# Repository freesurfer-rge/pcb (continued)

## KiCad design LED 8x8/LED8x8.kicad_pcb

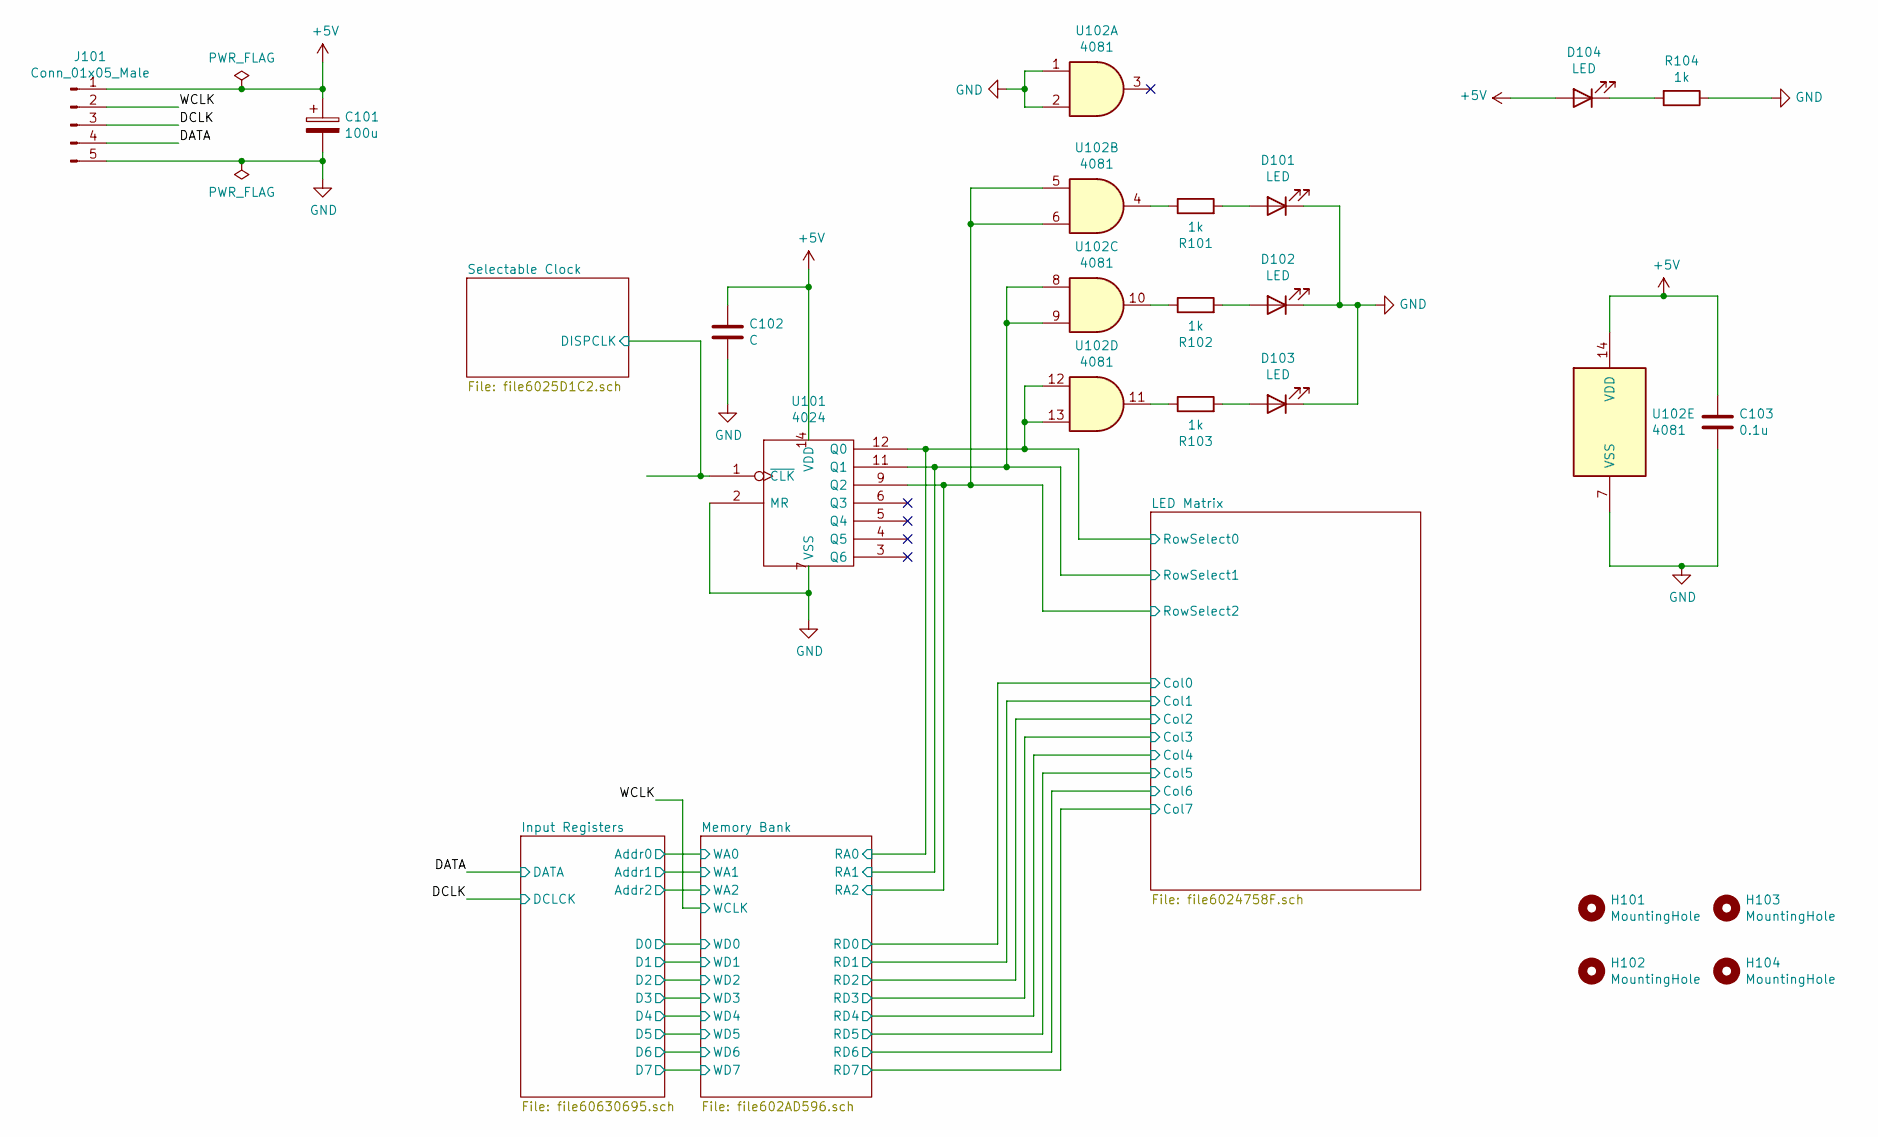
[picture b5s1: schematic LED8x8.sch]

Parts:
C101: 100u; CP_Radial_D5.0mm_P2.50mm
C102: C; C_Disc_D4.7mm_W2.5mm_P5.00mm
C103: 0.1u; C_Disc_D4.7mm_W2.5mm_P5.00mm
D101, D102, D103: LED; LED_D3.0mm
D104: LED; LED_D5.0mm
H101, H102, H103, H104: MountingHole; MountingHole_2.7mm_M2.5
J101: Conn_01x05_Male; PinHeader_1x05_P2.54mm_Vertical
R101, R102, R103, R104: 1k; R_Axial_DIN0207_L6.3mm_D2.5mm_P7.62mm_Horizontal
U101: 4024; DIP-14_W7.62mm_Socket
U102: 4081

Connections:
+5V: C101.1, C102.2, C103.2, D104.2 (A), J101.1, U101.14 (VDD), U102.14 (VDD); also elsewhere on the board
/DATA: J101.4; also elsewhere on the board
/DCLK: J101.3; also elsewhere on the board
/Memory Bank/RA0: U101.12 (Q0), U102.12, U102.13; also elsewhere on the board
/Memory Bank/RA1: U101.11 (Q1), U102.8, U102.9; also elsewhere on the board
/Memory Bank/RA2: U101.9 (Q2), U102.5, U102.6; also elsewhere on the board
/Selectable Clock/DISPCLK: U101.1 (~CLK); also elsewhere on the board
/WCLK: J101.2; also elsewhere on the board
GND: C101.2, C102.1, C103.1, D101.1 (K), D102.1 (K), D103.1 (K), J101.5, R104.1, U101.2 (MR), U101.7 (VSS), U102.1, U102.2, U102.7 (VSS); also elsewhere on the board
unnamed: D101.2 (A), R101.2
unnamed: D102.2 (A), R102.2
unnamed: D103.2 (A), R103.2
unnamed: D104.1 (K), R104.2
unnamed: R101.1, U102.4
unnamed: R102.1, U102.10
unnamed: R103.1, U102.11

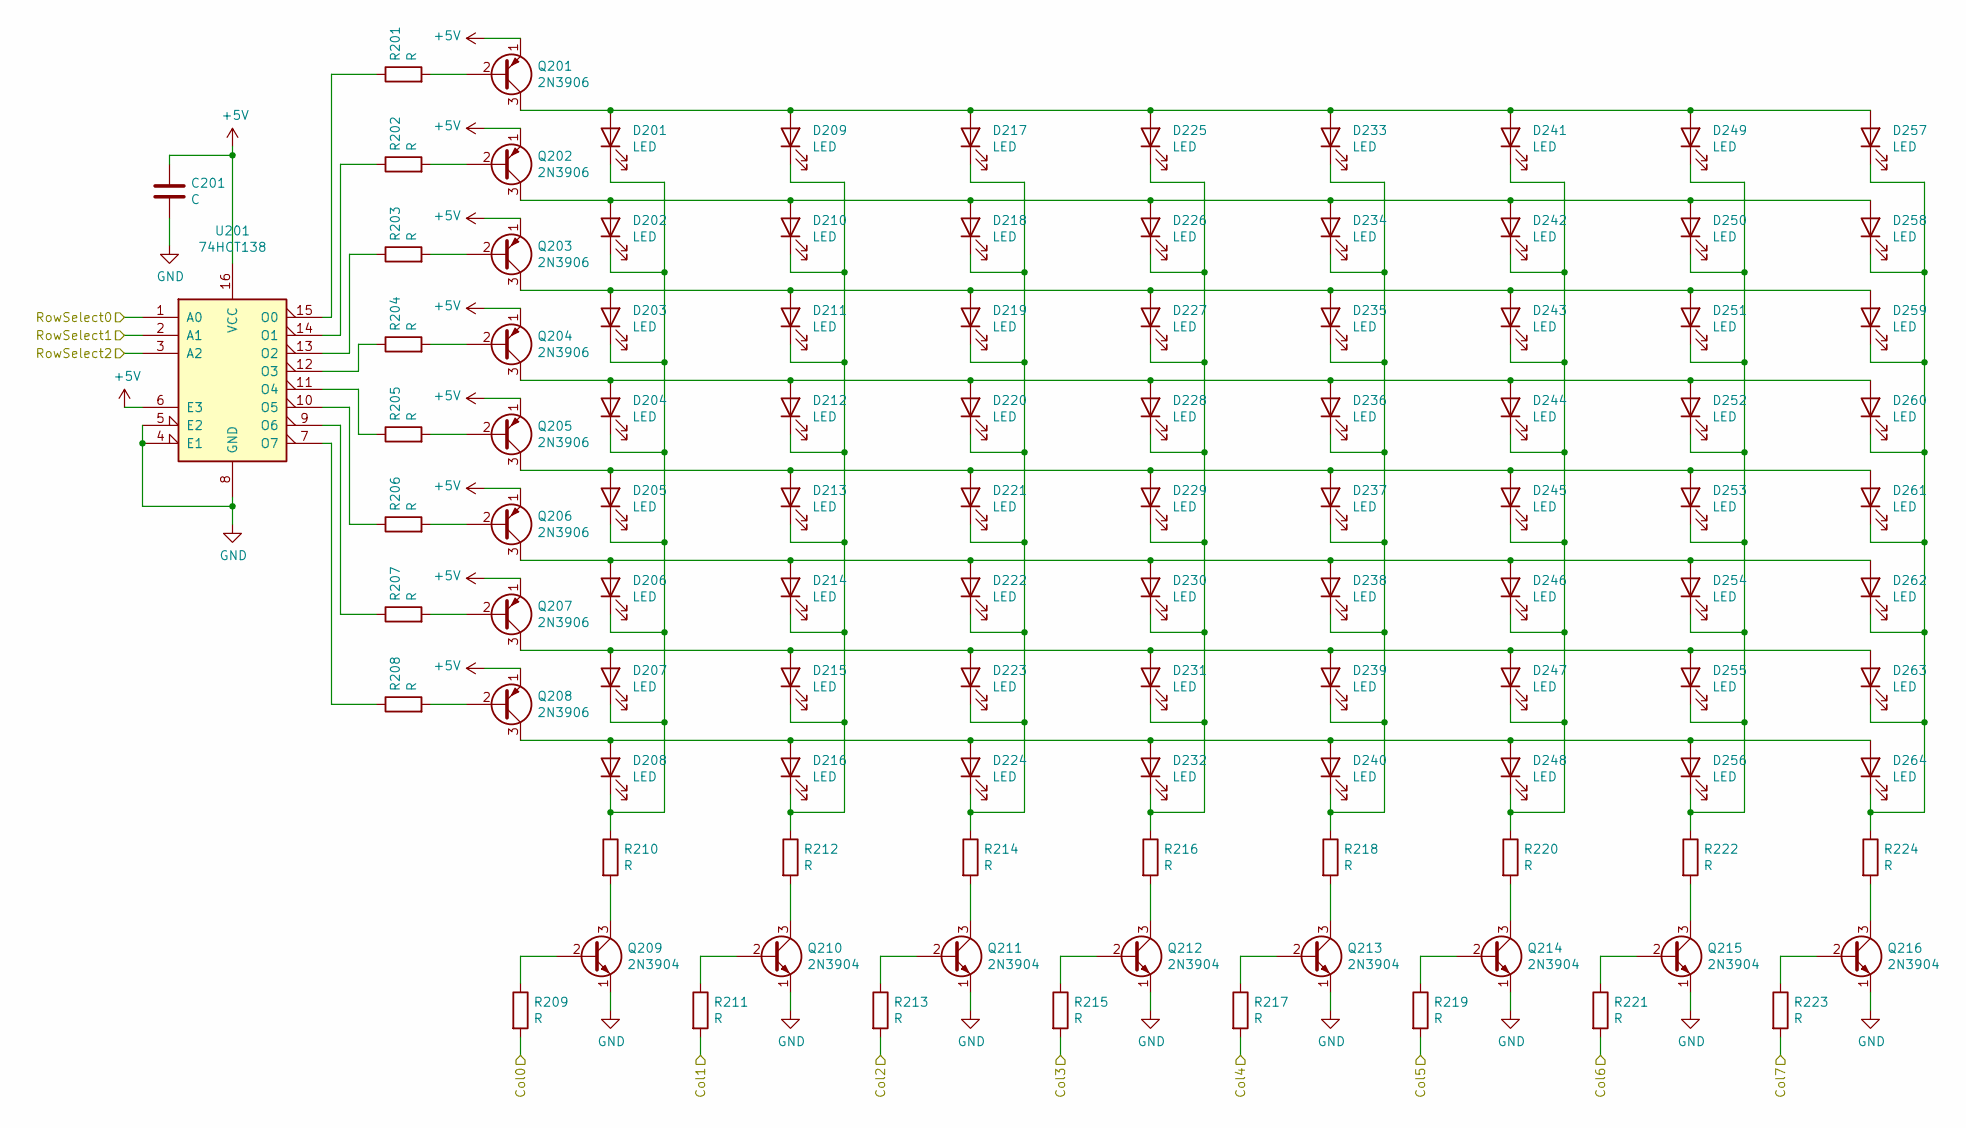
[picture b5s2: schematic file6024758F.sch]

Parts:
C201: C; C_Disc_D4.3mm_W1.9mm_P5.00mm
D201, D202, D203, D204, D205, D206, D207, D208, D209, D210, D211, D212, D213, D214, D215, D216, D217, D218, D219, D220, D221, D222, D223, D224, D225, D226, D227, D228, D229, D230, D231, D232, D233, D234, D235, D236, D237, D238, D239, D240, D241, D242, D243, D244, D245, D246, D247, D248, D249, D250, D251, D252, D253, D254, D255, D256, D257, D258, D259, D260, D261, D262, D263, D264: LED; LED_D5.0mm
Q201, Q202, Q203, Q204, Q205, Q206, Q207, Q208: 2N3906; TO-92_Wide
Q209, Q210, Q211, Q212, Q213, Q214, Q215, Q216: 2N3904; TO-92_Wide
R201, R202, R203, R204, R205, R206, R207, R208, R209, R210, R211, R212, R213, R214, R215, R216, R217, R218, R219, R220, R221, R222, R223, R224: R; R_Axial_DIN0207_L6.3mm_D2.5mm_P7.62mm_Horizontal
U201: 74HCT138; DIP-16_W7.62mm_Socket

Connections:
+5V: C201.2, Q201.1 (E), Q202.1 (E), Q203.1 (E), Q204.1 (E), Q205.1 (E), Q206.1 (E), Q207.1 (E), Q208.1 (E), U201.6 (E3), U201.16 (VCC); also elsewhere on the board
/LED Matrix/Col0: R209.2; also elsewhere on the board
/LED Matrix/Col1: R211.2; also elsewhere on the board
/LED Matrix/Col2: R213.2; also elsewhere on the board
/LED Matrix/Col3: R215.2; also elsewhere on the board
/LED Matrix/Col4: R217.2; also elsewhere on the board
/LED Matrix/Col5: R219.2; also elsewhere on the board
/LED Matrix/Col6: R221.2; also elsewhere on the board
/LED Matrix/Col7: R223.2; also elsewhere on the board
/Memory Bank/RA0: U201.1 (A0); also elsewhere on the board
/Memory Bank/RA1: U201.2 (A1); also elsewhere on the board
/Memory Bank/RA2: U201.3 (A2); also elsewhere on the board
GND: C201.1, Q209.1 (E), Q210.1 (E), Q211.1 (E), Q212.1 (E), Q213.1 (E), Q214.1 (E), Q215.1 (E), Q216.1 (E), U201.4 (E1), U201.5 (E2), U201.8 (GND); also elsewhere on the board
unnamed: D201.1 (K), D202.1 (K), D203.1 (K), D204.1 (K), D205.1 (K), D206.1 (K), D207.1 (K), D208.1 (K), R210.1
unnamed: D201.2 (A), D209.2 (A), D217.2 (A), D225.2 (A), D233.2 (A), D241.2 (A), D249.2 (A), D257.2 (A), Q201.3 (C)
unnamed: D202.2 (A), D210.2 (A), D218.2 (A), D226.2 (A), D234.2 (A), D242.2 (A), D250.2 (A), D258.2 (A), Q202.3 (C)
unnamed: D203.2 (A), D211.2 (A), D219.2 (A), D227.2 (A), D235.2 (A), D243.2 (A), D251.2 (A), D259.2 (A), Q203.3 (C)
unnamed: D204.2 (A), D212.2 (A), D220.2 (A), D228.2 (A), D236.2 (A), D244.2 (A), D252.2 (A), D260.2 (A), Q204.3 (C)
unnamed: D205.2 (A), D213.2 (A), D221.2 (A), D229.2 (A), D237.2 (A), D245.2 (A), D253.2 (A), D261.2 (A), Q205.3 (C)
unnamed: D206.2 (A), D214.2 (A), D222.2 (A), D230.2 (A), D238.2 (A), D246.2 (A), D254.2 (A), D262.2 (A), Q206.3 (C)
unnamed: D207.2 (A), D215.2 (A), D223.2 (A), D231.2 (A), D239.2 (A), D247.2 (A), D255.2 (A), D263.2 (A), Q207.3 (C)
unnamed: D208.2 (A), D216.2 (A), D224.2 (A), D232.2 (A), D240.2 (A), D248.2 (A), D256.2 (A), D264.2 (A), Q208.3 (C)
unnamed: D209.1 (K), D210.1 (K), D211.1 (K), D212.1 (K), D213.1 (K), D214.1 (K), D215.1 (K), D216.1 (K), R212.1
unnamed: D217.1 (K), D218.1 (K), D219.1 (K), D220.1 (K), D221.1 (K), D222.1 (K), D223.1 (K), D224.1 (K), R214.1
unnamed: D225.1 (K), D226.1 (K), D227.1 (K), D228.1 (K), D229.1 (K), D230.1 (K), D231.1 (K), D232.1 (K), R216.1
unnamed: D233.1 (K), D234.1 (K), D235.1 (K), D236.1 (K), D237.1 (K), D238.1 (K), D239.1 (K), D240.1 (K), R218.1
unnamed: D241.1 (K), D242.1 (K), D243.1 (K), D244.1 (K), D245.1 (K), D246.1 (K), D247.1 (K), D248.1 (K), R220.1
unnamed: D249.1 (K), D250.1 (K), D251.1 (K), D252.1 (K), D253.1 (K), D254.1 (K), D255.1 (K), D256.1 (K), R222.1
unnamed: D257.1 (K), D258.1 (K), D259.1 (K), D260.1 (K), D261.1 (K), D262.1 (K), D263.1 (K), D264.1 (K), R224.1
unnamed: Q201.2 (B), R201.2
unnamed: Q202.2 (B), R202.2
unnamed: Q203.2 (B), R203.2
unnamed: Q204.2 (B), R204.2
unnamed: Q205.2 (B), R205.2
unnamed: Q206.2 (B), R206.2
unnamed: Q207.2 (B), R207.2
unnamed: Q208.2 (B), R208.2
unnamed: Q209.2 (B), R209.1
unnamed: Q209.3 (C), R210.2
unnamed: Q210.2 (B), R211.1
unnamed: Q210.3 (C), R212.2
unnamed: Q211.2 (B), R213.1
unnamed: Q211.3 (C), R214.2
unnamed: Q212.2 (B), R215.1
unnamed: Q212.3 (C), R216.2
unnamed: Q213.2 (B), R217.1
unnamed: Q213.3 (C), R218.2
unnamed: Q214.2 (B), R219.1
unnamed: Q214.3 (C), R220.2
unnamed: Q215.2 (B), R221.1
unnamed: Q215.3 (C), R222.2
unnamed: Q216.2 (B), R223.1
unnamed: Q216.3 (C), R224.2
unnamed: R201.1, U201.15 (O0)
unnamed: R202.1, U201.14 (O1)
unnamed: R203.1, U201.13 (O2)
unnamed: R204.1, U201.12 (O3)
unnamed: R205.1, U201.11 (O4)
unnamed: R206.1, U201.10 (O5)
unnamed: R207.1, U201.9 (O6)
unnamed: R208.1, U201.7 (O7)

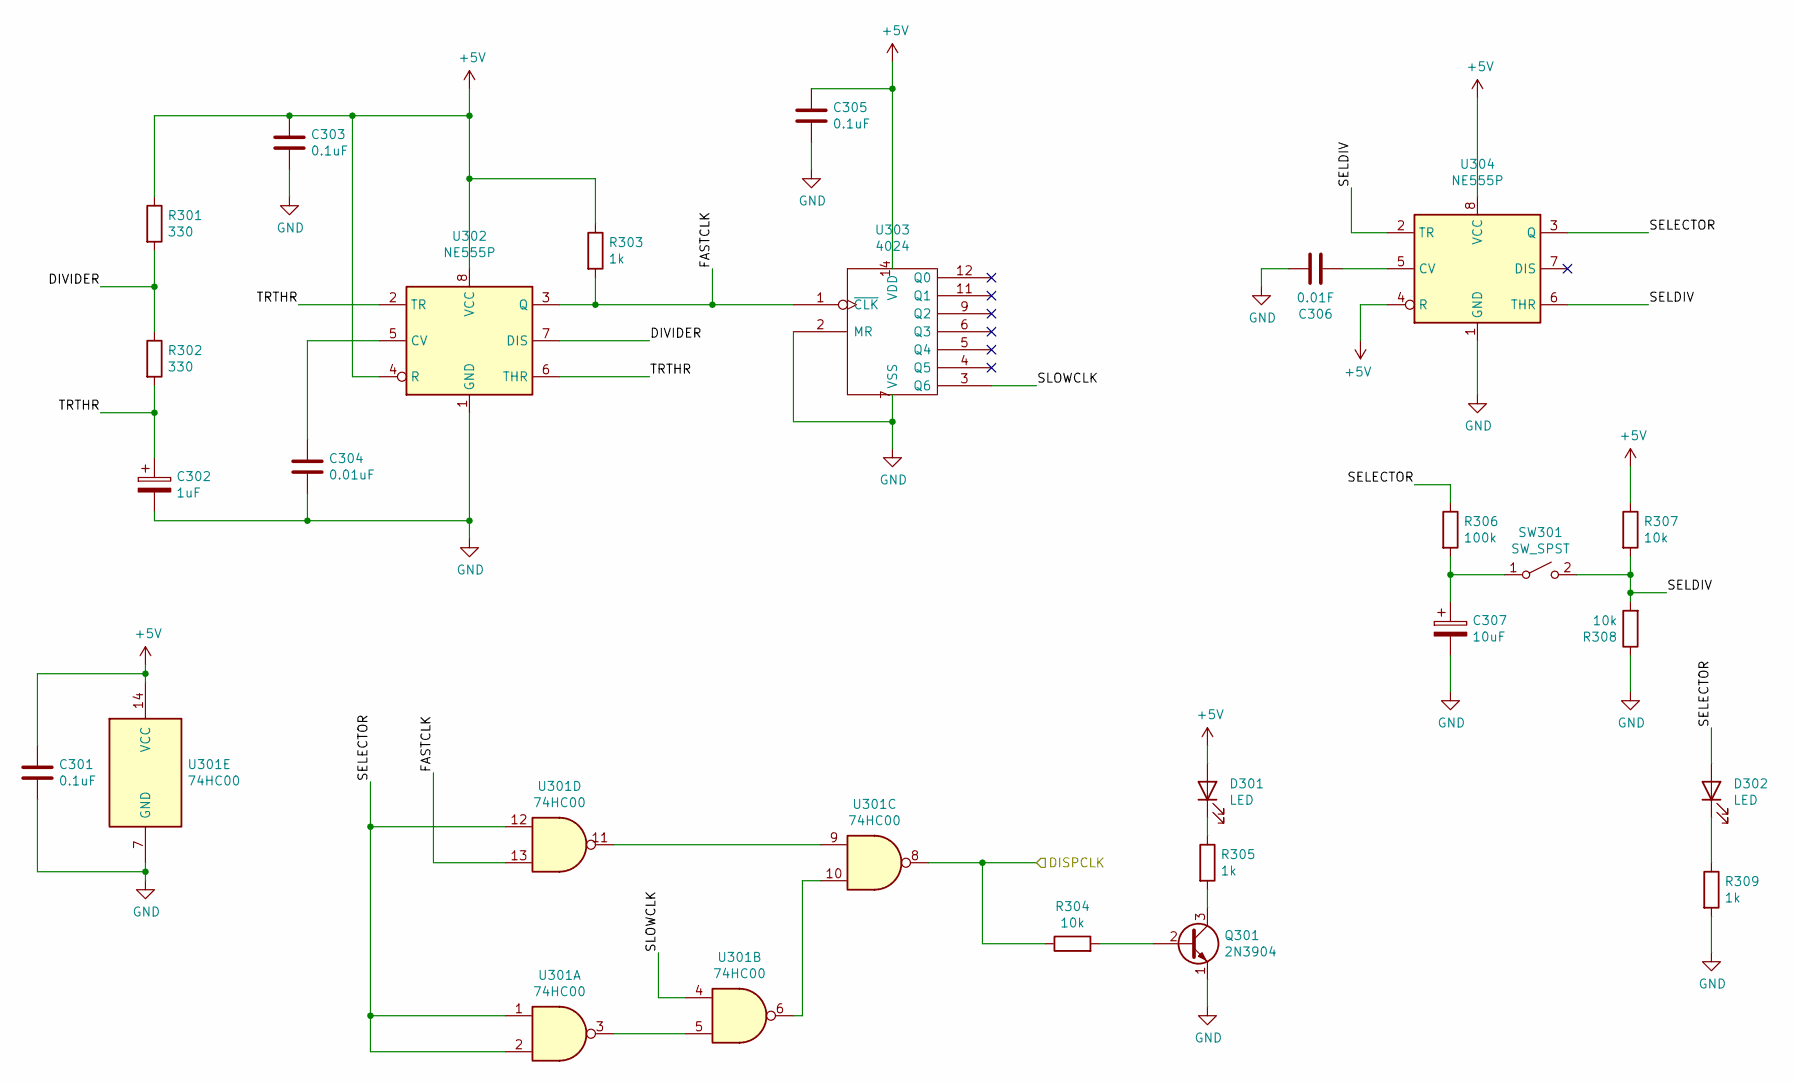
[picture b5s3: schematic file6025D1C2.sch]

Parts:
C301, C303, C305: 0.1uF; C_Disc_D4.3mm_W1.9mm_P5.00mm
C302: 1uF; CP_Radial_D4.0mm_P1.50mm
C304: 0.01uF; C_Disc_D3.8mm_W2.6mm_P2.50mm
C306: 0.01F; C_Disc_D3.4mm_W2.1mm_P2.50mm
C307: 10uF; CP_Radial_D4.0mm_P1.50mm
D301, D302: LED; LED_D5.0mm
Q301: 2N3904; TO-92_Wide
R301, R302: 330; R_Axial_DIN0207_L6.3mm_D2.5mm_P7.62mm_Horizontal
R303, R305, R309: 1k; R_Axial_DIN0207_L6.3mm_D2.5mm_P7.62mm_Horizontal
R304, R307, R308: 10k; R_Axial_DIN0207_L6.3mm_D2.5mm_P7.62mm_Horizontal
R306: 100k; R_Axial_DIN0207_L6.3mm_D2.5mm_P7.62mm_Horizontal
SW301: SW_SPST; SW_PUSH_6mm
U301: 74HC00; DIP-14_W7.62mm_Socket
U302, U304: NE555P; DIP-8_W7.62mm_Socket
U303: 4024; DIP-14_W7.62mm_Socket

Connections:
+5V: C301.2, C303.2, C305.2, D301.2 (A), R301.1, R303.1, R307.1, U301.14 (VCC), U302.4 (R), U302.8 (VCC), U303.14 (VDD), U304.4 (R), U304.8 (VCC); also elsewhere on the board
/Selectable Clock/DISPCLK: R304.1, U301.8; also elsewhere on the board
/Selectable Clock/DIVIDER: R301.2, R302.1, U302.7 (DIS)
/Selectable Clock/FASTCLK: R303.2, U301.13, U302.3 (Q), U303.1 (~CLK)
/Selectable Clock/SELDIV: R307.2, R308.2, SW301.2 (B), U304.2 (TR), U304.6 (THR)
/Selectable Clock/SELECTOR: D302.2 (A), R306.1, U301.1, U301.2, U301.12, U304.3 (Q)
/Selectable Clock/SLOWCLK: U301.4, U303.3 (Q6)
/Selectable Clock/TRTHR: C302.1, R302.2, U302.2 (TR), U302.6 (THR)
GND: C301.1, C302.2, C303.1, C304.2, C305.1, C306.2, C307.2, Q301.1 (E), R308.1, R309.2, U301.7 (GND), U302.1 (GND), U303.2 (MR), U303.7 (VSS), U304.1 (GND); also elsewhere on the board
unnamed: C304.1, U302.5 (CV)
unnamed: C306.1, U304.5 (CV)
unnamed: C307.1, R306.2, SW301.1 (A)
unnamed: D301.1 (K), R305.1
unnamed: D302.1 (K), R309.1
unnamed: Q301.2 (B), R304.2
unnamed: Q301.3 (C), R305.2
unnamed: U301.3, U301.5
unnamed: U301.6, U301.10
unnamed: U301.9, U301.11

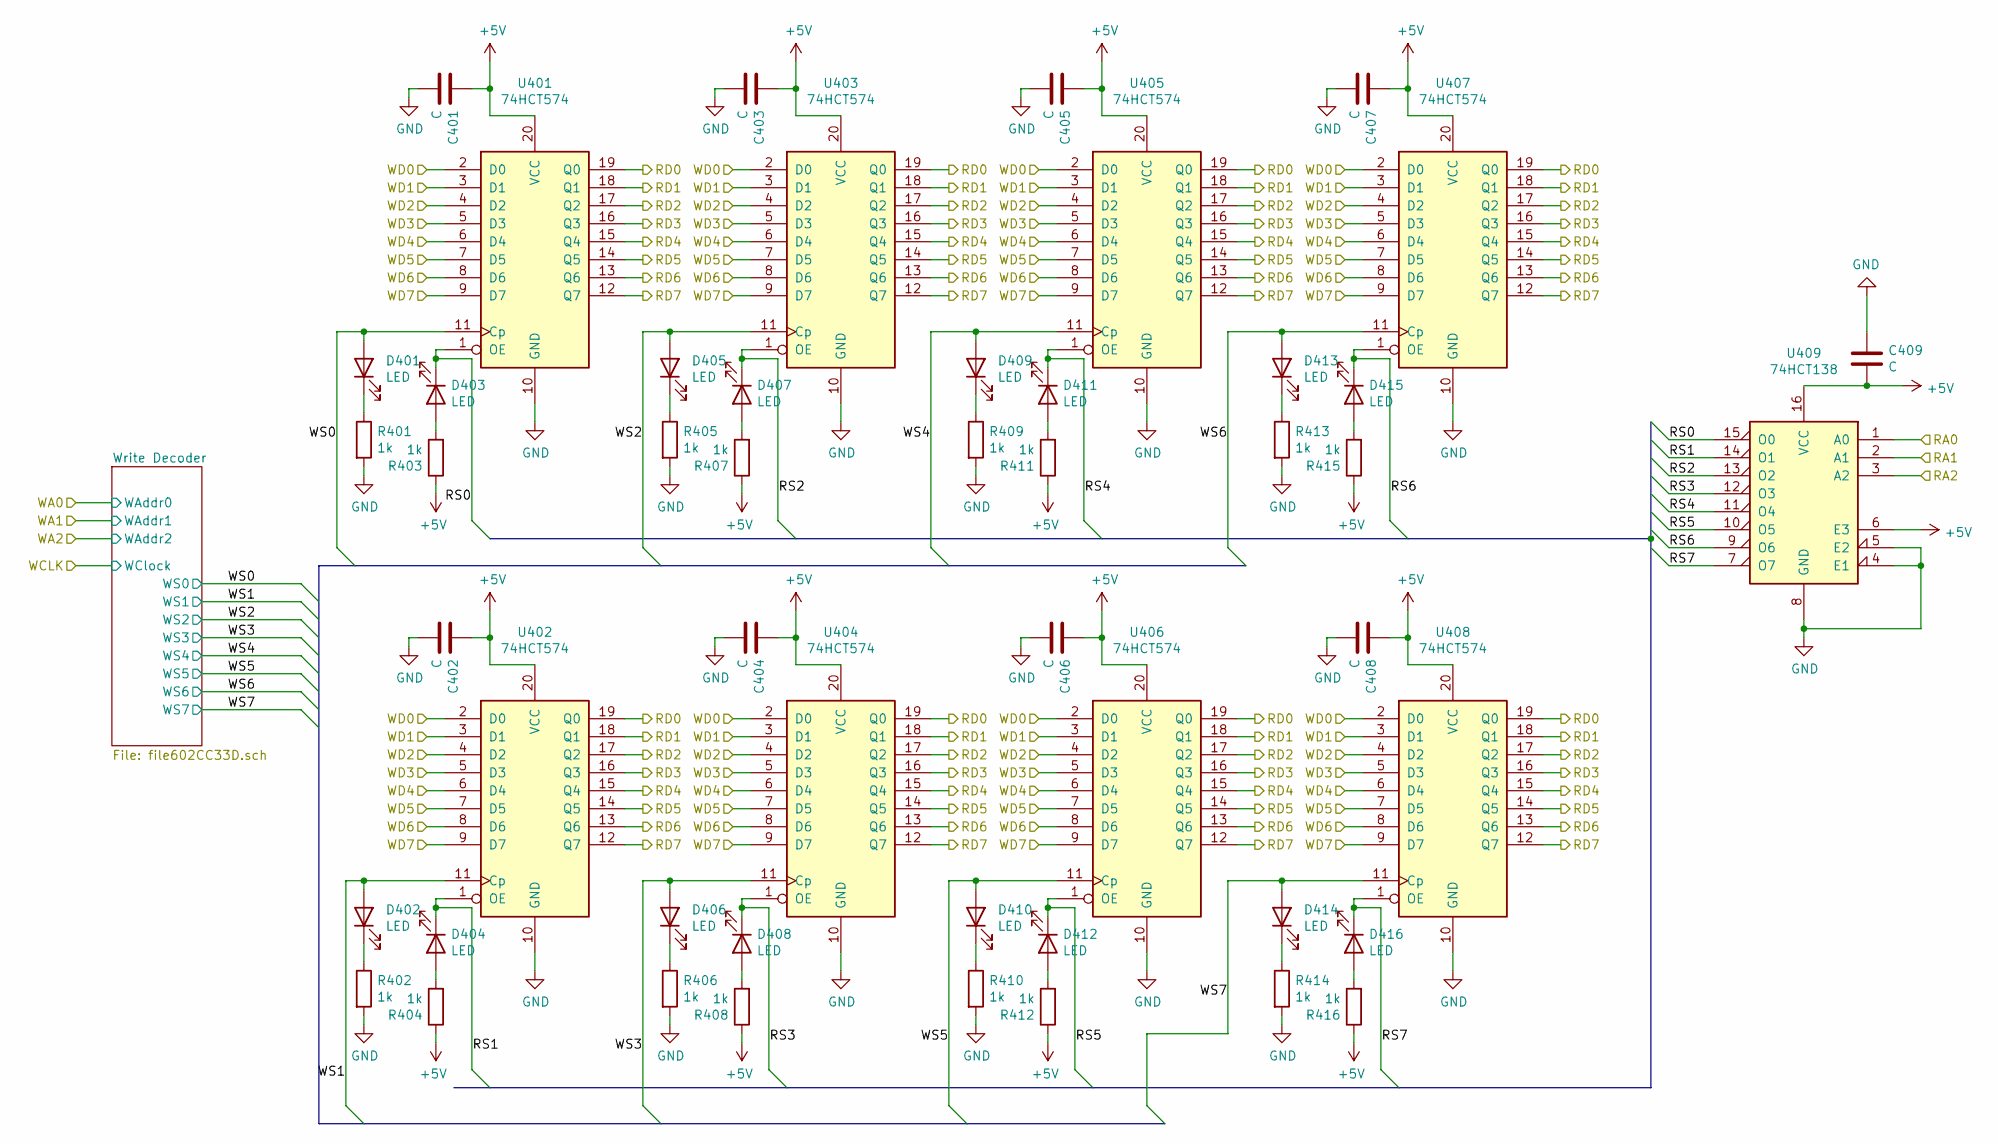
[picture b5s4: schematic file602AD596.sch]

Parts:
C401, C402, C403, C404, C405, C406, C407, C408, C409: C; C_Disc_D4.3mm_W1.9mm_P5.00mm
D401, D402, D403, D404, D405, D406, D407, D408, D409, D410, D411, D412, D413, D414, D415, D416: LED; LED_D3.0mm
R401, R402, R403, R404, R405, R406, R407, R408, R409, R410, R411, R412, R413, R414, R415, R416: 1k; R_Axial_DIN0207_L6.3mm_D2.5mm_P7.62mm_Horizontal
U401, U402, U403, U404, U405, U406, U407, U408: 74HCT574; DIP-20_W7.62mm_Socket
U409: 74HCT138; DIP-16_W7.62mm_Socket

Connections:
+5V: C401.2, C402.2, C403.2, C404.2, C405.2, C406.2, C407.2, C408.2, C409.2, R403.1, R404.1, R407.1, R408.1, R411.1, R412.1, R415.1, R416.1, U401.20 (VCC), U402.20 (VCC), U403.20 (VCC), U404.20 (VCC), U405.20 (VCC), U406.20 (VCC), U407.20 (VCC), U408.20 (VCC), U409.6 (E3), U409.16 (VCC); also elsewhere on the board
/Input Registers/D0: U401.2 (D0), U402.2 (D0), U403.2 (D0), U404.2 (D0), U405.2 (D0), U406.2 (D0), U407.2 (D0), U408.2 (D0); also elsewhere on the board
/Input Registers/D1: U401.3 (D1), U402.3 (D1), U403.3 (D1), U404.3 (D1), U405.3 (D1), U406.3 (D1), U407.3 (D1), U408.3 (D1); also elsewhere on the board
/Input Registers/D2: U401.4 (D2), U402.4 (D2), U403.4 (D2), U404.4 (D2), U405.4 (D2), U406.4 (D2), U407.4 (D2), U408.4 (D2); also elsewhere on the board
/Input Registers/D3: U401.5 (D3), U402.5 (D3), U403.5 (D3), U404.5 (D3), U405.5 (D3), U406.5 (D3), U407.5 (D3), U408.5 (D3); also elsewhere on the board
/Input Registers/D4: U401.6 (D4), U402.6 (D4), U403.6 (D4), U404.6 (D4), U405.6 (D4), U406.6 (D4), U407.6 (D4), U408.6 (D4); also elsewhere on the board
/Input Registers/D5: U401.7 (D5), U402.7 (D5), U403.7 (D5), U404.7 (D5), U405.7 (D5), U406.7 (D5), U407.7 (D5), U408.7 (D5); also elsewhere on the board
/Input Registers/D6: U401.8 (D6), U402.8 (D6), U403.8 (D6), U404.8 (D6), U405.8 (D6), U406.8 (D6), U407.8 (D6), U408.8 (D6); also elsewhere on the board
/Input Registers/D7: U401.9 (D7), U402.9 (D7), U403.9 (D7), U404.9 (D7), U405.9 (D7), U406.9 (D7), U407.9 (D7), U408.9 (D7); also elsewhere on the board
/LED Matrix/Col0: U401.19 (Q0), U402.19 (Q0), U403.19 (Q0), U404.19 (Q0), U405.19 (Q0), U406.19 (Q0), U407.19 (Q0), U408.19 (Q0); also elsewhere on the board
/LED Matrix/Col1: U401.18 (Q1), U402.18 (Q1), U403.18 (Q1), U404.18 (Q1), U405.18 (Q1), U406.18 (Q1), U407.18 (Q1), U408.18 (Q1); also elsewhere on the board
/LED Matrix/Col2: U401.17 (Q2), U402.17 (Q2), U403.17 (Q2), U404.17 (Q2), U405.17 (Q2), U406.17 (Q2), U407.17 (Q2), U408.17 (Q2); also elsewhere on the board
/LED Matrix/Col3: U401.16 (Q3), U402.16 (Q3), U403.16 (Q3), U404.16 (Q3), U405.16 (Q3), U406.16 (Q3), U407.16 (Q3), U408.16 (Q3); also elsewhere on the board
/LED Matrix/Col4: U401.15 (Q4), U402.15 (Q4), U403.15 (Q4), U404.15 (Q4), U405.15 (Q4), U406.15 (Q4), U407.15 (Q4), U408.15 (Q4); also elsewhere on the board
/LED Matrix/Col5: U401.14 (Q5), U402.14 (Q5), U403.14 (Q5), U404.14 (Q5), U405.14 (Q5), U406.14 (Q5), U407.14 (Q5), U408.14 (Q5); also elsewhere on the board
/LED Matrix/Col6: U401.13 (Q6), U402.13 (Q6), U403.13 (Q6), U404.13 (Q6), U405.13 (Q6), U406.13 (Q6), U407.13 (Q6), U408.13 (Q6); also elsewhere on the board
/LED Matrix/Col7: U401.12 (Q7), U402.12 (Q7), U403.12 (Q7), U404.12 (Q7), U405.12 (Q7), U406.12 (Q7), U407.12 (Q7), U408.12 (Q7); also elsewhere on the board
/Memory Bank/RA0: U409.1 (A0); also elsewhere on the board
/Memory Bank/RA1: U409.2 (A1); also elsewhere on the board
/Memory Bank/RA2: U409.3 (A2); also elsewhere on the board
/Memory Bank/RS0: D403.1 (K), U401.1 (OE), U409.15 (O0)
/Memory Bank/RS1: D404.1 (K), U402.1 (OE), U409.14 (O1)
/Memory Bank/RS2: D407.1 (K), U403.1 (OE), U409.13 (O2)
/Memory Bank/RS3: D408.1 (K), U404.1 (OE), U409.12 (O3)
/Memory Bank/RS4: D411.1 (K), U405.1 (OE), U409.11 (O4)
/Memory Bank/RS5: D412.1 (K), U406.1 (OE), U409.10 (O5)
/Memory Bank/RS6: D415.1 (K), U407.1 (OE), U409.9 (O6)
/Memory Bank/RS7: D416.1 (K), U408.1 (OE), U409.7 (O7)
/Memory Bank/WS0: D401.2 (A), U401.11 (Cp); also elsewhere on the board
/Memory Bank/WS1: D402.2 (A), U402.11 (Cp); also elsewhere on the board
/Memory Bank/WS2: D405.2 (A), U403.11 (Cp); also elsewhere on the board
/Memory Bank/WS3: D406.2 (A), U404.11 (Cp); also elsewhere on the board
/Memory Bank/WS4: D409.2 (A), U405.11 (Cp); also elsewhere on the board
/Memory Bank/WS5: D410.2 (A), U406.11 (Cp); also elsewhere on the board
/Memory Bank/WS6: D413.2 (A), U407.11 (Cp); also elsewhere on the board
/Memory Bank/WS7: D414.2 (A), U408.11 (Cp); also elsewhere on the board
GND: C401.1, C402.1, C403.1, C404.1, C405.1, C406.1, C407.1, C408.1, C409.1, R401.2, R402.2, R405.2, R406.2, R409.2, R410.2, R413.2, R414.2, U401.10 (GND), U402.10 (GND), U403.10 (GND), U404.10 (GND), U405.10 (GND), U406.10 (GND), U407.10 (GND), U408.10 (GND), U409.4 (E1), U409.5 (E2), U409.8 (GND); also elsewhere on the board
unnamed: D401.1 (K), R401.1
unnamed: D402.1 (K), R402.1
unnamed: D403.2 (A), R403.2
unnamed: D404.2 (A), R404.2
unnamed: D405.1 (K), R405.1
unnamed: D406.1 (K), R406.1
unnamed: D407.2 (A), R407.2
unnamed: D408.2 (A), R408.2
unnamed: D409.1 (K), R409.1
unnamed: D410.1 (K), R410.1
unnamed: D411.2 (A), R411.2
unnamed: D412.2 (A), R412.2
unnamed: D413.1 (K), R413.1
unnamed: D414.1 (K), R414.1
unnamed: D415.2 (A), R415.2
unnamed: D416.2 (A), R416.2

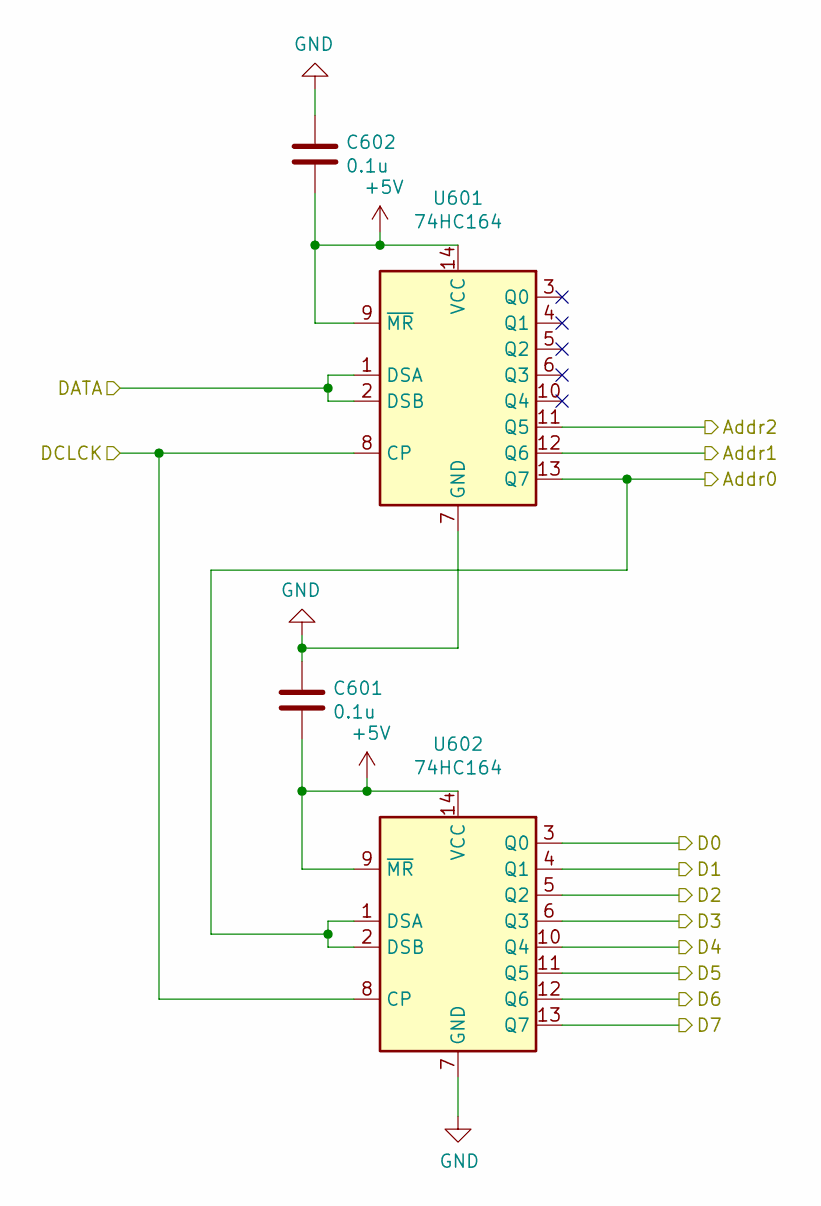
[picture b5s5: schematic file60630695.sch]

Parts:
C601, C602: 0.1u; C_Disc_D4.3mm_W1.9mm_P5.00mm
U601, U602: 74HC164; DIP-14_W7.62mm_Socket

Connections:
+5V: C601.2, C602.2, U601.9 (~MR), U601.14 (VCC), U602.9 (~MR), U602.14 (VCC); also elsewhere on the board
/DATA: U601.1 (DSA), U601.2 (DSB); also elsewhere on the board
/DCLK: U601.8 (CP), U602.8 (CP); also elsewhere on the board
/Input Registers/Addr0: U601.13 (Q7), U602.1 (DSA), U602.2 (DSB); also elsewhere on the board
/Input Registers/Addr1: U601.12 (Q6); also elsewhere on the board
/Input Registers/Addr2: U601.11 (Q5); also elsewhere on the board
/Input Registers/D0: U602.3 (Q0); also elsewhere on the board
/Input Registers/D1: U602.4 (Q1); also elsewhere on the board
/Input Registers/D2: U602.5 (Q2); also elsewhere on the board
/Input Registers/D3: U602.6 (Q3); also elsewhere on the board
/Input Registers/D4: U602.10 (Q4); also elsewhere on the board
/Input Registers/D5: U602.11 (Q5); also elsewhere on the board
/Input Registers/D6: U602.12 (Q6); also elsewhere on the board
/Input Registers/D7: U602.13 (Q7); also elsewhere on the board
GND: C601.1, C602.1, U601.7 (GND), U602.7 (GND); also elsewhere on the board

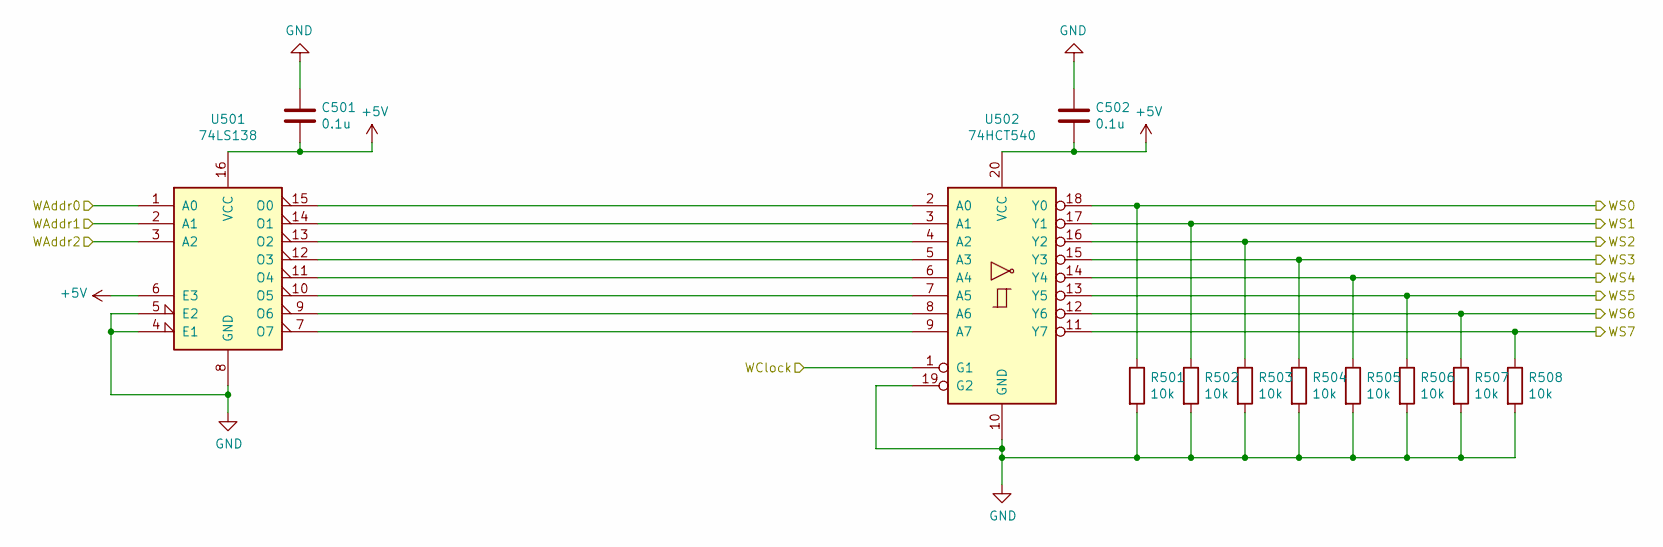
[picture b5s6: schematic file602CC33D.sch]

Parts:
C501, C502: 0.1u; C_Disc_D4.3mm_W1.9mm_P5.00mm
R501, R502, R503, R504, R505, R506, R507, R508: 10k; R_Axial_DIN0207_L6.3mm_D2.5mm_P7.62mm_Horizontal
U501: 74LS138; DIP-16_W7.62mm_Socket
U502: 74HCT540; DIP-20_W7.62mm_Socket

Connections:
+5V: C501.2, C502.2, U501.6 (E3), U501.16 (VCC), U502.20 (VCC); also elsewhere on the board
/Input Registers/Addr0: U501.1 (A0); also elsewhere on the board
/Input Registers/Addr1: U501.2 (A1); also elsewhere on the board
/Input Registers/Addr2: U501.3 (A2); also elsewhere on the board
/Memory Bank/WS0: R501.1, U502.18 (Y0); also elsewhere on the board
/Memory Bank/WS1: R502.1, U502.17 (Y1); also elsewhere on the board
/Memory Bank/WS2: R503.1, U502.16 (Y2); also elsewhere on the board
/Memory Bank/WS3: R504.1, U502.15 (Y3); also elsewhere on the board
/Memory Bank/WS4: R505.1, U502.14 (Y4); also elsewhere on the board
/Memory Bank/WS5: R506.1, U502.13 (Y5); also elsewhere on the board
/Memory Bank/WS6: R507.1, U502.12 (Y6); also elsewhere on the board
/Memory Bank/WS7: R508.1, U502.11 (Y7); also elsewhere on the board
/WCLK: U502.1 (G1); also elsewhere on the board
GND: C501.1, C502.1, R501.2, R502.2, R503.2, R504.2, R505.2, R506.2, R507.2, R508.2, U501.4 (E1), U501.5 (E2), U501.8 (GND), U502.10 (GND), U502.19 (G2); also elsewhere on the board
unnamed: U501.7 (O7), U502.9 (A7)
unnamed: U501.9 (O6), U502.8 (A6)
unnamed: U501.10 (O5), U502.7 (A5)
unnamed: U501.11 (O4), U502.6 (A4)
unnamed: U501.12 (O3), U502.5 (A3)
unnamed: U501.13 (O2), U502.4 (A2)
unnamed: U501.14 (O1), U502.3 (A1)
unnamed: U501.15 (O0), U502.2 (A0)

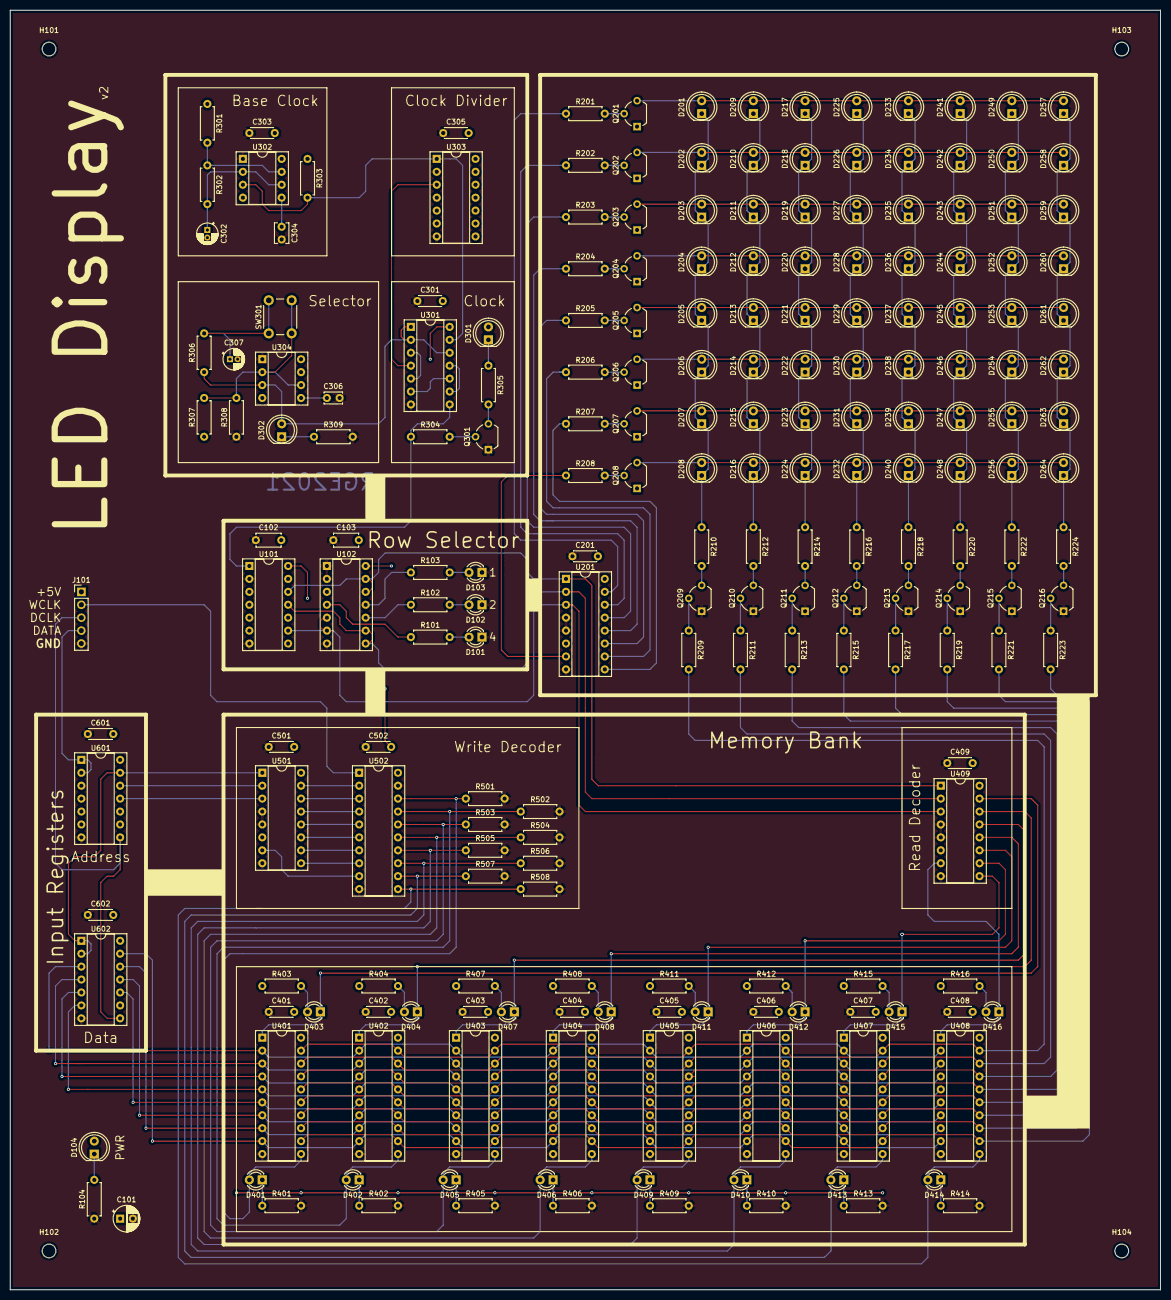
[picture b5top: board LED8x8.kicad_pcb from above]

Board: 2 copper layers, 226.1 x 251.5 mm, 214 parts (0 on the bottom side), 139 nets.
